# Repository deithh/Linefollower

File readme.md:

# Line Follower Robot  

## Overview  
This repository contains the project of a Line Follower Robot developed as part of the Computer Systems Architecture course at the Poznan University of Technology. The robot is designed to autonomously follow a black line on a flat surface using embedded sensors and self-developed control logic. The project involved designing, assembling, and programming the robot from scratch.  

**We managed to create an autonomous system that can follow the line at a speed of approximately 0.6 m/s**  
We won a competition outperforming 10 other teams with our creation of a lightweight robot featuring an efficient drive system.  

## Team Members  
1. Hubert Błaszczyk - 155085
- PCB etching
- Software development
- Video production
- System testing and calibration

2. Bartosz Operacz - 155957
- PCB etching
- Software development
- Documentation preparation
- System testing and calibration

3. **I was responible for:**
- PCB etching
- Robot design
- Component assembly
- System testing and calibration  

## Project Goal
The objective of the project was to develop a robot capable of autonomously tracking a black line by:

- Detecting a black line beneath it  
- Operating on a flat surface with the ability to steer and adjust speed  
- Being self-powered  
- Generating signals to follow the line accurately  
- Indicating correct operation through LEDs  
- Allowing easy reprogramming for improvements or troubleshooting  

## Technical Specifications
- Sensors: 5 TCRT5000 optical sensors to detect line position.
- Motors: 2 N20-BT16 motors with 2000 rpm, allowing ~2 m/s speed.
- Motor Driver: TB6612FNG for dual-channel motor control.
- Power Source: 2S 7.4V Li-Pol battery.
- Voltage Regulator: LM7805 with reverse current protection.
- Microcontroller: ATMEGA328P-PN, 16MHz clock.
- Other Features: Custom PCB with solder mask, LED indicators, programmable SPI interface.

## Software Overview
The software was developed to:  

Read sensor signals to determine the robot's position relative to the line.
Control motor speed and direction based on a PID (Proportional-Integral-Derivative) controller.
Use LEDs to signal operational status and low battery levels.
Key Functions:

drive_motors: Controls motor speed and direction.
calibrate: Calibrates the sensors for line detection.
calculate_error: Calculates deviation from the line.
PID control: Adjusts motor speed to correct positioning.
Assembly and Etching
The PCB etching process was completed in-house, following these steps:

Preparing film layouts.
UV exposure and etching.
Drilling and mounting components.
Final soldering and assembly.

## Budget Summary
The total cost for the project components was approximately 404.53 PLN.

## Demo Video
A video demonstration of the Line Follower Robot is available on YouTube:  
[result](https://youtu.be/YW8YQgWOzjk)  
[project video](https://www.youtube.com/watch?v=wPkWPQ8s4SI&ab_channel=NapewnonieHubert)  

## Notes
Capacitor C5 was removed due to programming issues.  
The footprint for LM7805 was incorrectly sized, requiring adjustments.

### Project documentation is available in polish

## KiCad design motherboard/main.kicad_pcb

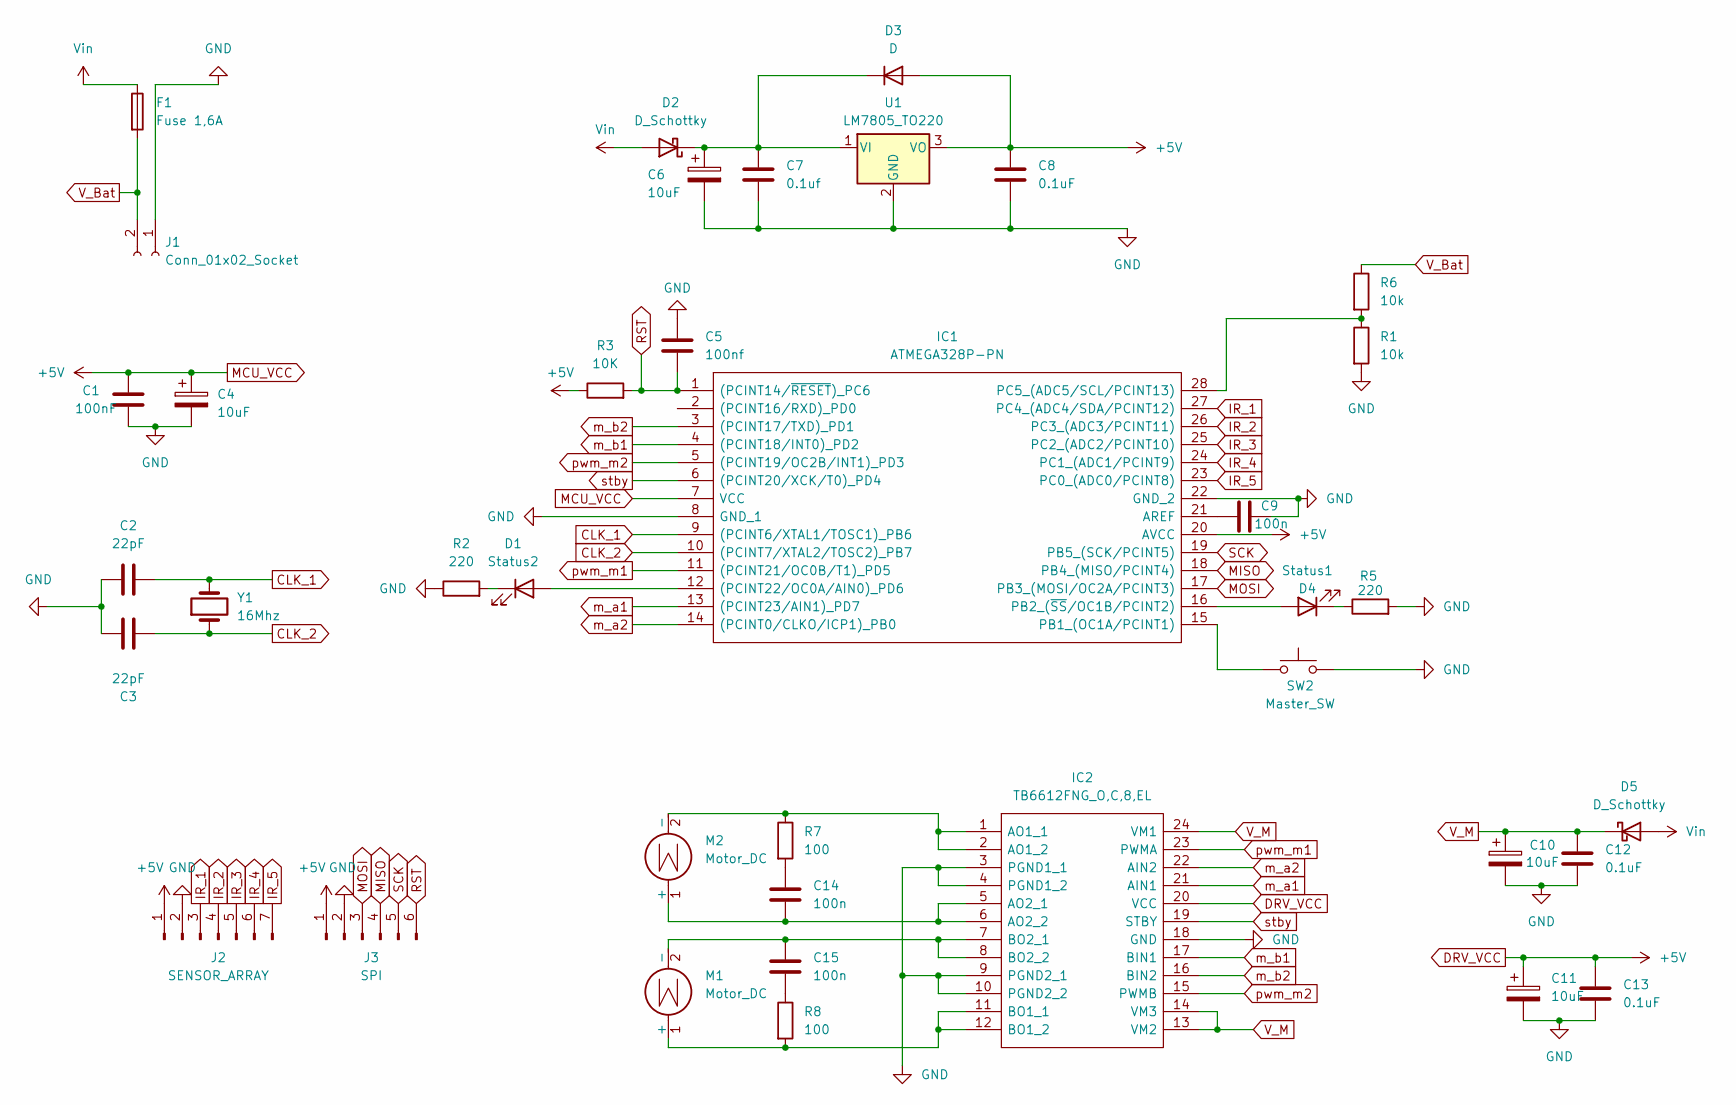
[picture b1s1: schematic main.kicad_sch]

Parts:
C1: 100nF; C_Rect_L4.6mm_W2.0mm_P2.50mm_MKS02_FKP02
C2, C3: 22pF; C_Rect_L4.6mm_W2.0mm_P2.50mm_MKS02_FKP02
C4, C6, C10, C11: 10uF; CP_Radial_D5.0mm_P2.00mm
C5: 100nf; C_Rect_L4.6mm_W5.5mm_P2.50mm_MKS02_FKP02
C7: 0.1uf; C_Rect_L4.6mm_W2.0mm_P2.50mm_MKS02_FKP02
C8, C12, C13: 0.1uF; C_Rect_L4.6mm_W2.0mm_P2.50mm_MKS02_FKP02
C9, C14, C15: 100n; C_Rect_L4.6mm_W2.0mm_P2.50mm_MKS02_FKP02
D1: Status2; LED_D3.0mm_FlatTop
D2, D5: D_Schottky; D_DO-201AD_P15.24mm_Horizontal
D3: D; R_Axial_DIN0207_L6.3mm_D2.5mm_P10.16mm_Horizontal
D4: Status1; LED_D3.0mm_FlatTop
F1: Fuse 1,6A; C_Disc_D5.1mm_W3.2mm_P5.00mm
IC1: ATMEGA328P-PN; DIP794W53P254L3467H457Q28N; Manufacturer_Part_Number ATMEGA328P-PN
IC2: TB6612FNG_O,C,8,EL; SOP65P760X160-24N; Manufacturer_Part_Number TB6612FNG(O,C,8,EL
J1: Conn_01x02_Socket; JST_XH_B2B-XH-A_1x02_P2.50mm_Vertical
J2: SENSOR_ARRAY; PinHeader_1x07_P2.54mm_Horizontal
J3: SPI; PinHeader_1x06_P2.54mm_Vertical
M1, M2: Motor_DC; JST_XH_B2B-XH-A_1x02_P2.50mm_Vertical
R1, R6: 10k; R_Axial_DIN0207_L6.3mm_D2.5mm_P10.16mm_Horizontal
R2, R5: 220; R_Axial_DIN0207_L6.3mm_D2.5mm_P10.16mm_Horizontal
R3: 10K; R_Axial_DIN0207_L6.3mm_D2.5mm_P10.16mm_Horizontal
R7, R8: 100; R_Axial_DIN0207_L6.3mm_D2.5mm_P10.16mm_Horizontal
SW2: Master_SW; SW_PUSH_6mm_H4.3mm
U1: LM7805_TO220; TO-3P-3_Vertical
Y1: 16Mhz; Crystal_HC49-4H_Vertical

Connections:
CLK_1: C2.2, IC1.9 ((PCINT6/XTAL1/TOSC1)_PB6), Y1.2
CLK_2: C3.1, IC1.10 ((PCINT7/XTAL2/TOSC2)_PB7), Y1.1
DRV_VCC: C1.1, C4.1, C8.1, C11.1, C13.2, D3.2 (A), IC1.7 (VCC), IC1.20 (AVCC), IC2.20 (VCC), J2.1, J3.1, R3.1, U1.3 (VO)
GND: C1.2, C2.1, C3.2, C4.2, C5.1, C6.2, C7.2, C8.2, C9.2, C10.2, C11.2, C12.2, C13.1, IC1.8 (GND_1), IC1.22 (GND_2), IC2.3 (PGND1_1), IC2.4 (PGND1_2), IC2.9 (PGND2_1), IC2.10 (PGND2_2), IC2.18 (GND), J1.1, J2.2, J3.2, R1.2, R2.1, R5.2, SW2.2, U1.2 (GND)
IR_1: IC1.27 (PC4_(ADC4/SDA/PCINT12)), J2.3
IR_2: IC1.26 (PC3_(ADC3/PCINT11)), J2.4
IR_3: IC1.25 (PC2_(ADC2/PCINT10)), J2.5
IR_4: IC1.24 (PC1_(ADC1/PCINT9)), J2.6
IR_5: IC1.23 (PC0_(ADC0/PCINT8)), J2.7
MISO: IC1.18 (PB4_(MISO/PCINT4)), J3.4
MOSI: IC1.17 (PB3_(MOSI/OC2A/PCINT3)), J3.3
unnamed: C14.1, R7.2
unnamed: C15.2, R8.1
unnamed: D1.2 (A), IC1.12 ((PCINT22/OC0A/AIN0)_PD6)
unnamed: D1.1 (K), R2.2
unnamed: C6.1, C7.1, D2.1 (K), D3.1 (K), U1.1 (VI)
unnamed: D4.2 (A), IC1.16 (PB2_(~SS/OC1B/PCINT2))
unnamed: D4.1 (K), R5.1
unnamed: C9.1, IC1.21 (AREF)
unnamed: IC1.15 (PB1_(OC1A/PCINT1)), SW2.1
unnamed: IC1.28 (PC5_(ADC5/SCL/PCINT13)), R1.1, R6.2
unnamed: IC2.1 (AO1_1), IC2.2 (AO1_2), M2.2 (-), R7.1
unnamed: C14.2, IC2.5 (AO2_1), IC2.6 (AO2_2), M2.1 (+)
unnamed: IC2.11 (BO1_1), IC2.12 (BO1_2), M1.1 (+), R8.2
unnamed: C15.1, IC2.7 (BO2_1), IC2.8 (BO2_2), M1.2 (-)
RST: C5.2, IC1.1 ((PCINT14/~RESET)_PC6), J3.6, R3.2
SCK: IC1.19 (PB5_(SCK/PCINT5)), J3.5
V_Bat: F1.2, J1.2, R6.1
V_M: C10.1, C12.1, D5.1 (K), IC2.13 (VM2), IC2.14 (VM3), IC2.24 (VM1)
Vin: D2.2 (A), D5.2 (A), F1.1
m_a1: IC1.13 ((PCINT23/AIN1)_PD7), IC2.21 (AIN1)
m_a2: IC1.14 ((PCINT0/CLKO/ICP1)_PB0), IC2.22 (AIN2)
m_b1: IC1.4 ((PCINT18/INT0)_PD2), IC2.17 (BIN1)
m_b2: IC1.3 ((PCINT17/TXD)_PD1), IC2.16 (BIN2)
pwm_m1: IC1.11 ((PCINT21/OC0B/T1)_PD5), IC2.23 (PWMA)
pwm_m2: IC1.5 ((PCINT19/OC2B/INT1)_PD3), IC2.15 (PWMB)
stby: IC1.6 ((PCINT20/XCK/T0)_PD4), IC2.19 (STBY)

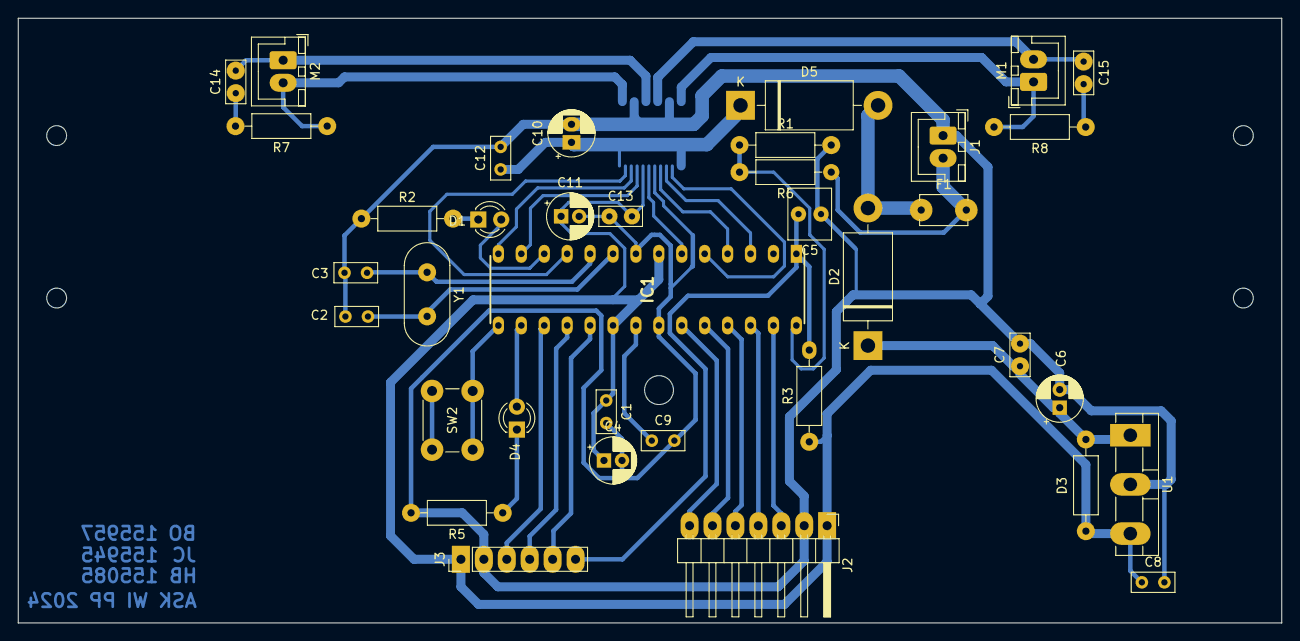
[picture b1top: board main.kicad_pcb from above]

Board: 2 copper layers, 140.0 x 67.0 mm, 38 parts (1 on the bottom side), 37 nets.

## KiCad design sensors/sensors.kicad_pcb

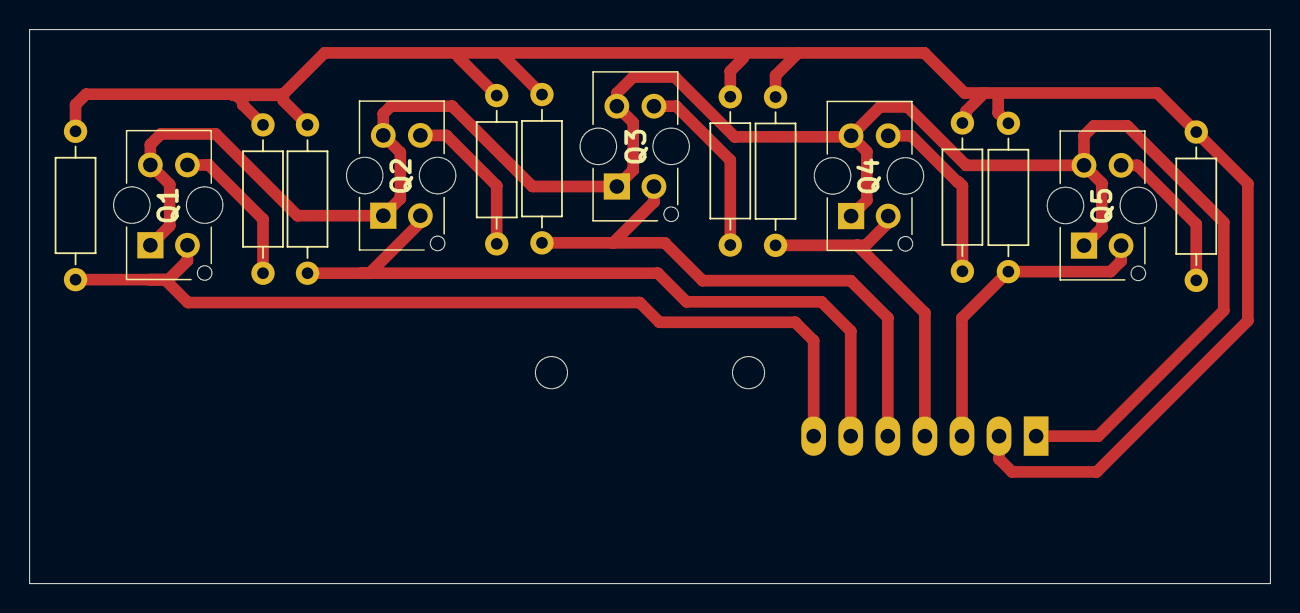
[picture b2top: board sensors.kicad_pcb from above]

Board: 2 copper layers, 85.0 x 38.0 mm, 16 parts (1 on the bottom side), 12 nets.

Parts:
J1: Conn_01x07_Pin; PinHeader_1x07_P2.54mm_Horizontal
Q1, Q2, Q3, Q4, Q5: TCRT5000
R1, R2, R3, R4, R5, R6, R7, R8, R9, R10: R; R_Axial_DIN0207_L6.3mm_D2.5mm_P10.16mm_Horizontal

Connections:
+5V: J1.7, Q1.1 (C), Q1.4 (A), Q2.1 (C), Q2.4 (A), Q3.1 (C), Q3.4 (A), Q4.1 (C), Q4.4 (A), Q5.1 (C), Q5.4 (A)
GND: J1.6, R1.2, R2.2, R3.2, R4.2, R5.2, R6.2, R7.2, R8.2, R9.2, R10.2
unnamed: Q1.3 (K), R2.1
unnamed: Q2.3 (K), R4.1
unnamed: Q3.3 (K), R6.1
unnamed: Q4.3 (K), R8.1
unnamed: Q5.3 (K), R10.1
Out_1: J1.1, Q1.2 (E), R1.1
Out_2: J1.2, Q2.2 (E), R3.1
Out_3: J1.3, Q3.2 (E), R5.1
Out_4: J1.4, Q4.2 (E), R7.1
Out_5: J1.5, Q5.2 (E), R9.1

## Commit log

2024-10-26 upload
